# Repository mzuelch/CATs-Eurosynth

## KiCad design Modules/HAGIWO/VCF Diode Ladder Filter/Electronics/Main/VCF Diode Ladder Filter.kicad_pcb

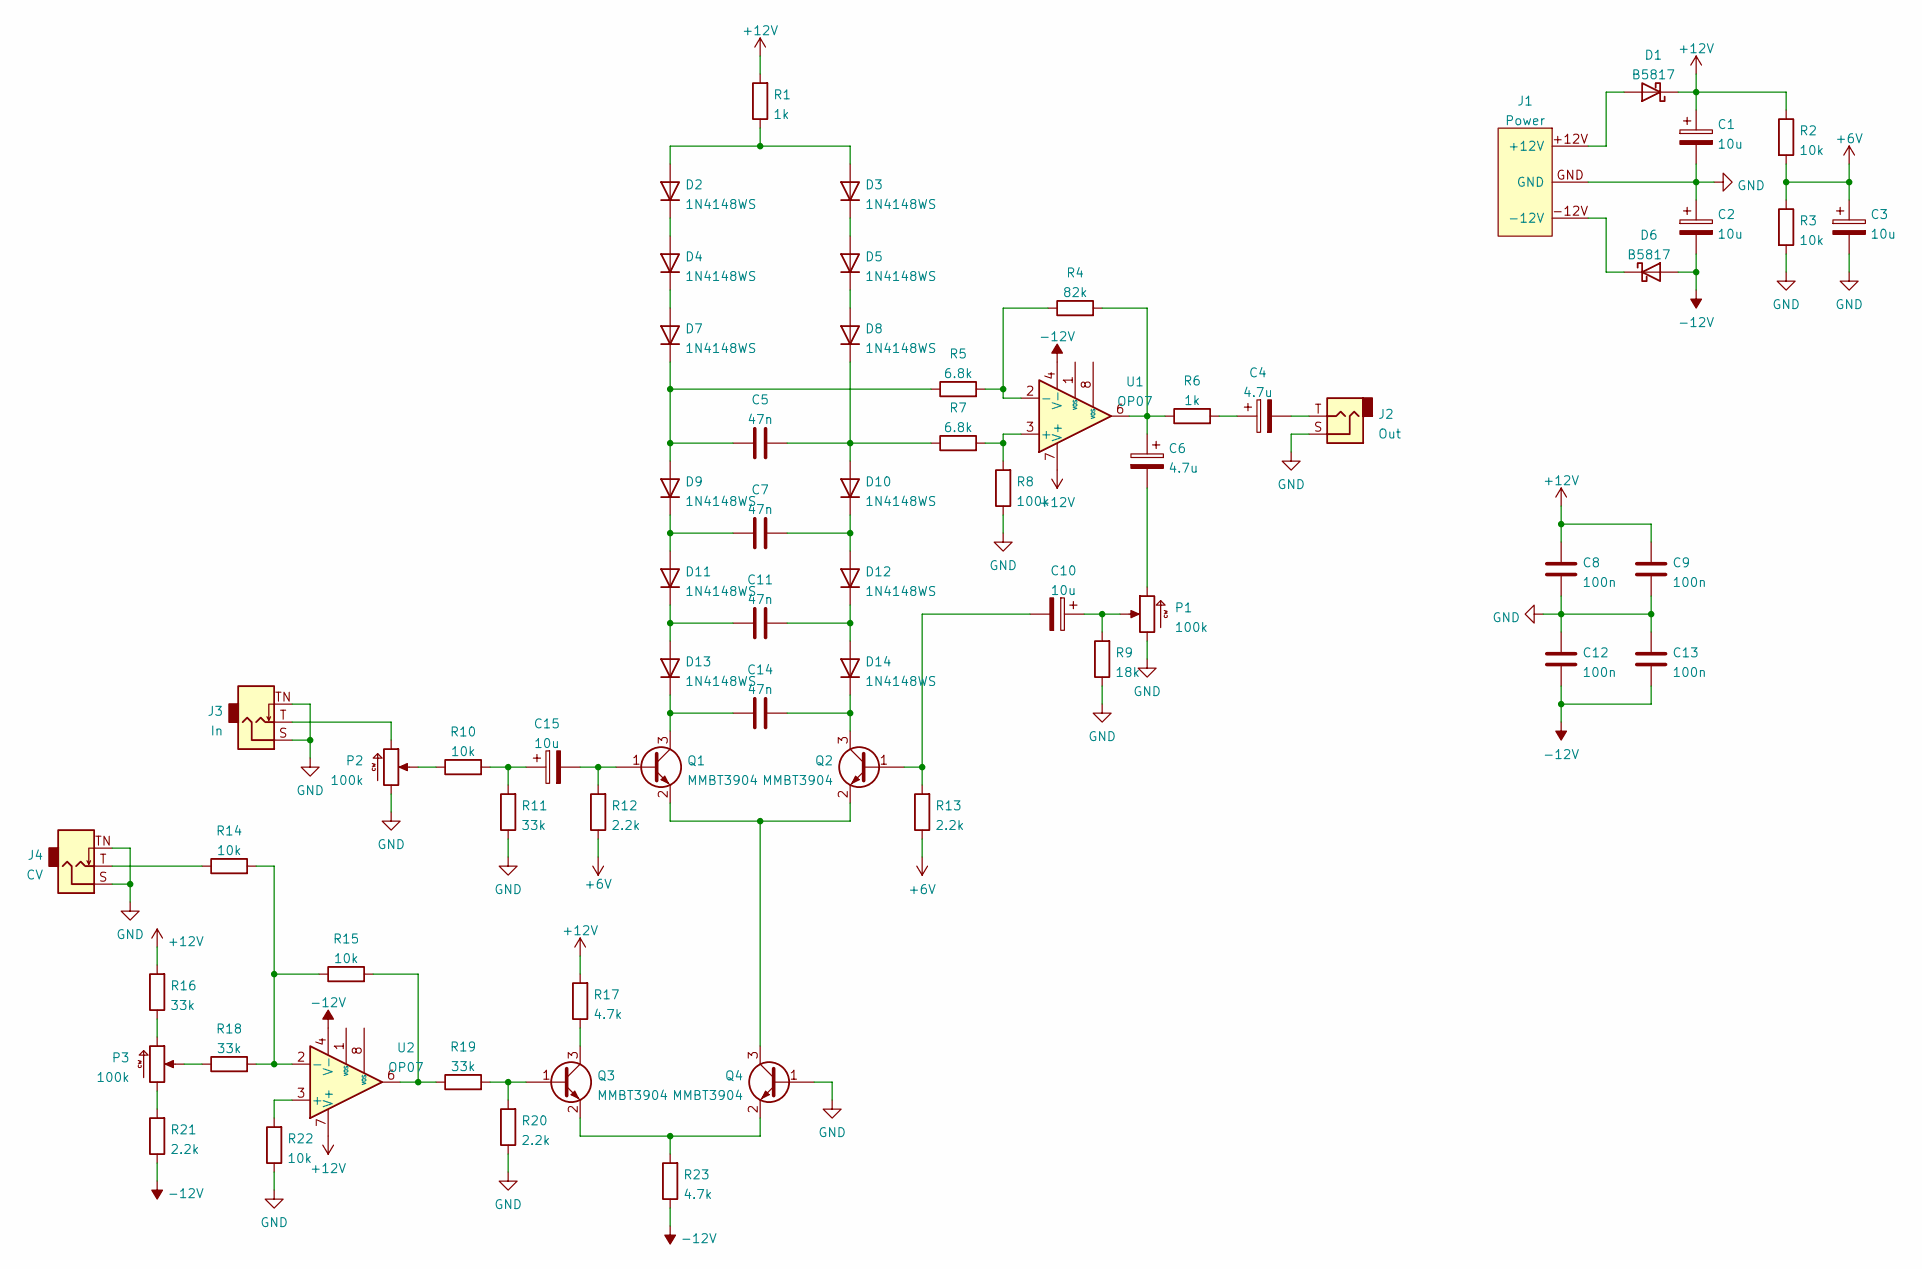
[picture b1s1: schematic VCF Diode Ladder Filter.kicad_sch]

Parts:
C1, C2, C3, C10, C15: 10u; CP_Elec_4x5.4; LCSC C72485
C4, C6: 4.7u; CP_Elec_6.3x5.4; LCSC C90266
C5, C7, C11, C14: 47n; C_1206_3216Metric; LCSC C21812
C8, C9, C12, C13: 100n; C_0402_1005Metric; LCSC C307331
D1, D6: B5817; D_SOD-323; LCSC C122854
D2, D3, D4, D5, D7, D8, D9, D10, D11, D12, D13, D14: 1N4148WS; D_SOD-323; LCSC C2128
J1: Power; Power_2x5_Vertical
J2: Out; Jack_3.5mm_QingPu_WQP-PJ301M-12
J3: In; Jack_3.5mm_QingPu_WQP-PJ301M-12
J4: CV; Jack_3.5mm_QingPu_WQP-PJ301M-12
P1, P3: 100k; Potentiometer_AlpsAlpine_RK09L1140
P2: 100k; Potentiometer_AlpsAlpine_RK09K1130
Q1, Q2, Q3, Q4: MMBT3904; SOT-23; LCSC C20526
R1, R6: 1k; R_0402_1005Metric; LCSC C25905
R2, R3, R10, R14, R15, R22: 10k; R_0402_1005Metric; LCSC C25744
R4: 82k; R_0402_1005Metric; LCSC C4142
R5, R7: 6.8k; R_0402_1005Metric; LCSC C25917
R8: 100k; R_0402_1005Metric; LCSC C25741
R9: 18k; R_0402_1005Metric; LCSC C25762
R11, R16, R18, R19: 33k; R_0402_1005Metric; LCSC C25779
R12, R13, R20, R21: 2.2k; R_0402_1005Metric; LCSC C25879
R17, R23: 4.7k; R_0402_1005Metric; LCSC C25900
U1, U2: OP07; SOIC-8_3.9x4.9mm_P1.27mm; LCSC C7433

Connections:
+6V: C3.1, R2.2, R3.1, R12.1, R13.1
+12V: C1.1, C8.1, C9.1, D1.1 (K), R1.2, R2.1, R16.2, R17.2, U1.7 (V+), U2.7 (V+)
-12V: C2.2, C12.2, C13.2, D6.2 (A), R21.1, R23.1, U1.4 (V-), U2.4 (V-)
GND: C1.2, C2.1, C3.2, C8.2, C9.2, C12.1, C13.1, J1.GND, J2.S, J3.S, J3.TN, J4.S, J4.TN, P1.CCW, P2.CCW, Q4.1 (B), R3.2, R8.1, R9.1, R11.1, R20.1, R22.1
unnamed: C4.1, R6.2
unnamed: C4.2, J2.T
unnamed: C5.1, D7.1 (K), D9.2 (A), R5.1
unnamed: C5.2, D8.1 (K), D10.2 (A), R7.1
unnamed: C6.1, R4.2, R6.1, U1.6
unnamed: C6.2, P1.CW
unnamed: C7.1, D9.1 (K), D11.2 (A)
unnamed: C7.2, D10.1 (K), D12.2 (A)
unnamed: C10.1, P1.W, R9.2
unnamed: C10.2, Q2.1 (B), R13.2
unnamed: C11.1, D11.1 (K), D13.2 (A)
unnamed: C11.2, D12.1 (K), D14.2 (A)
unnamed: C14.1, D13.1 (K), Q1.3 (C)
unnamed: C14.2, D14.1 (K), Q2.3 (C)
unnamed: C15.1, R10.2, R11.2
unnamed: C15.2, Q1.1 (B), R12.2
unnamed: D1.2 (A), J1.+12V
unnamed: D2.1 (K), D4.2 (A)
unnamed: D2.2 (A), D3.2 (A), R1.1
unnamed: D3.1 (K), D5.2 (A)
unnamed: D4.1 (K), D7.2 (A)
unnamed: D5.1 (K), D8.2 (A)
unnamed: D6.1 (K), J1.-12V
unnamed: J3.T, P2.CW
unnamed: J4.T, R14.1
unnamed: P2.W, R10.1
unnamed: P3.CCW, R21.2
unnamed: P3.CW, R16.1
unnamed: P3.W, R18.1
unnamed: Q1.2 (E), Q2.2 (E), Q4.3 (C)
unnamed: Q3.1 (B), R19.2, R20.2
unnamed: Q3.2 (E), Q4.2 (E), R23.2
unnamed: Q3.3 (C), R17.1
unnamed: R4.1, R5.2, U1.2 (-)
unnamed: R7.2, R8.2, U1.3 (+)
unnamed: R14.2, R15.1, R18.2, U2.2 (-)
unnamed: R15.2, R19.1, U2.6
unnamed: R22.2, U2.3 (+)

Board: 2 copper layers, 65 parts (59 on the bottom side), 42 nets, no tracks yet.

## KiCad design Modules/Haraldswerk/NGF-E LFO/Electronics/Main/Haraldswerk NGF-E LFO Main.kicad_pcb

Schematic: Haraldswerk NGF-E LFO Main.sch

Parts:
C1: 1µF; C_Disc_D4.7mm_W2.5mm_P5.00mm
C2, C3: 10µF; CP_Radial_D4.0mm_P1.50mm
C4, C5, C6, C7, C8, C9: 100n; C_Disc_D4.7mm_W2.5mm_P5.00mm
C10: 10µF; C_Disc_D4.7mm_W2.5mm_P5.00mm
C11: 2.2µF; C_Disc_D4.7mm_W2.5mm_P5.00mm
D1, D2: LED; LED_D3.0mm
D3, D4: B5819; D_DO-41_SOD81_P7.62mm_Horizontal
J1: SAW_UP; Jack_3.5mm_QingPu_WQP-PJ323M
J2: SAW_DOWN; Jack_3.5mm_QingPu_WQP-PJ323M
J3: TRIANGLE; Jack_3.5mm_QingPu_WQP-PJ323M
J4: SQUARE; Jack_3.5mm_QingPu_WQP-PJ323M
J5: Power; Power_2x5_Vertical
J6: Select; PinHeader_2x03_P2.54mm_Vertical
Q1: BC547; TO-92_Inline
R1: 47; R_Axial_DIN0207_L6.3mm_D2.5mm_P2.54mm_Vertical
R2, R3: 68k; R_Axial_DIN0207_L6.3mm_D2.5mm_P2.54mm_Vertical
R4, R5, R9, R10, R11: 100k; R_Axial_DIN0207_L6.3mm_D2.5mm_P2.54mm_Vertical
R6, R7: 2k; R_Axial_DIN0207_L6.3mm_D2.5mm_P2.54mm_Vertical
R8: 47k; R_Axial_DIN0207_L6.3mm_D2.5mm_P2.54mm_Vertical
R12, R15, R16, R17: 1k; R_Axial_DIN0207_L6.3mm_D2.5mm_P2.54mm_Vertical
R13, R14: 10k; R_Axial_DIN0207_L6.3mm_D2.5mm_P2.54mm_Vertical
R18: 2k7; R_Axial_DIN0207_L6.3mm_D2.5mm_P2.54mm_Vertical
RV1: A100k; Potentiometer_AlpsAlpine_RK0971110
T1: 1k; Potentiometer_Runtron_RM-065_Vertical
U1, U2, U3: TL072; DIP-8_W7.62mm_LongPads

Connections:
+12V: C2.1, C4.1, C6.1, C8.1, D3.1 (K), U1.8 (V+), U2.8 (V+), U3.8 (V+)
+12VA: D3.2 (A), J5.+12V
-12V: C3.2, C5.2, C7.2, C9.2, D4.2 (A), U1.4 (V-), U2.4 (V-), U3.4 (V-)
-12VA: D4.1 (K), J5.-12V
GND: C2.2, C3.1, C4.2, C5.1, C6.2, C7.1, C8.2, C9.1, J1.S, J2.S, J3.S, J4.S, J5.GND, Q1.3 (E), R1.1, R3.1, R7.1, U1.6 (-), U2.5 (+), U3.5 (+)
unnamed: C1.2, J6.6
unnamed: C10.2, J6.2
unnamed: C11.2, J6.4
unnamed: D1.1 (K), D2.2 (A), U3.7
unnamed: D1.2 (A), D2.1 (K), R18.2, U3.6 (-)
unnamed: J1.T, R12.1
unnamed: J2.T, R15.1
unnamed: J3.T, R16.1
unnamed: J4.T, R17.1
unnamed: J6.1, J6.3, J6.5, R2.1, U1.2 (-)
unnamed: Q1.1 (C), R10.1, U2.3 (+)
unnamed: Q1.2 (B), R8.1
unnamed: R3.2, U1.3 (+)
unnamed: R4.1, R5.2, U1.5 (+)
unnamed: R6.1, T1.3
unnamed: R6.2, U1.7
unnamed: R7.2, T1.1
unnamed: R11.1, R12.2, R13.2, U2.1
unnamed: R9.1, R11.2, U2.2 (-)
unnamed: R13.1, R14.2, U2.6 (-)
unnamed: R14.1, R15.2, U2.7
unnamed: R17.2, U3.1, U3.2 (-)
SQR: R5.1, R8.2, T1.2, U3.3 (+)
TRI: C1.1, C10.1, C11.1, R4.2, R9.2, R10.2, R16.2, R18.1, U1.1

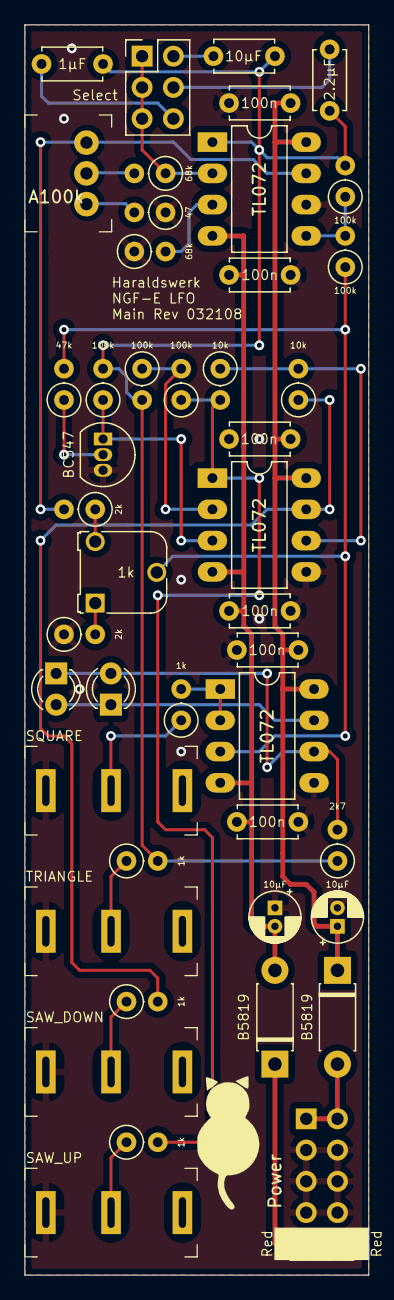
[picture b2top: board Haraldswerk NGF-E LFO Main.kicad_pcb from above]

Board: 2 copper layers, 27.9 x 101.6 mm, 45 parts (0 on the bottom side), 29 nets.

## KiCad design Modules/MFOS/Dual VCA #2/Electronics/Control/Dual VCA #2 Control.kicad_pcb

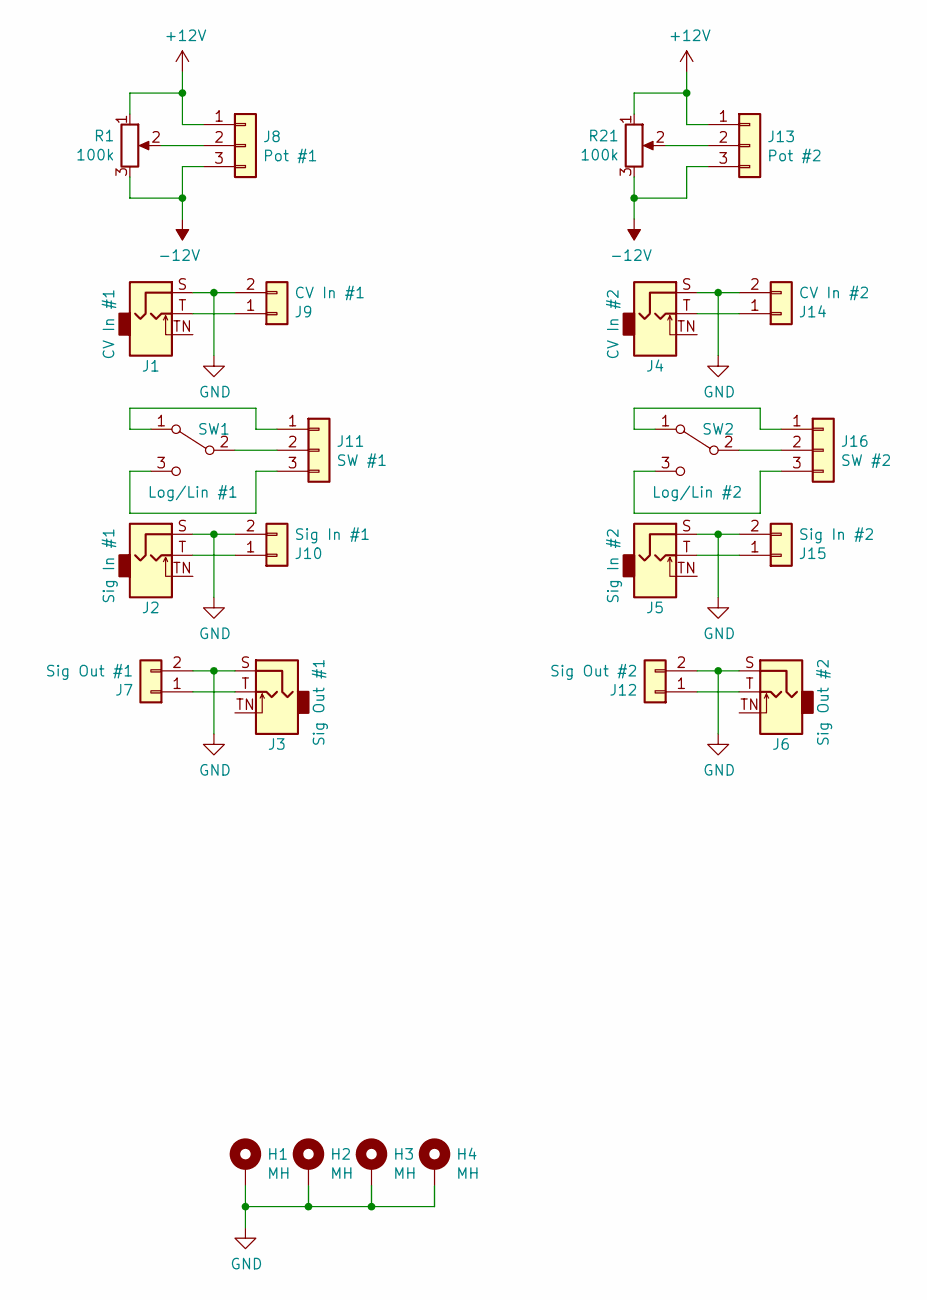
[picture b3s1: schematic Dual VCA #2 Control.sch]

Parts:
H1, H2, H3, H4: MH; MountingHole_2.7mm_M2.5_DIN965_Pad
J1: CV In #1; PJ-301-M-12
J2: Sig In #1; PJ-301-M-12
J3: Sig Out #1; PJ-301-M-12
J4: CV In #2; PJ-301-M-12
J5: Sig In #2; PJ-301-M-12
J6: Sig Out #2; PJ-301-M-12
J7: Sig Out #1; PinSocket_1x02_P2.54mm_Vertical
J8: Pot #1; PinSocket_1x03_P2.54mm_Vertical
J9: CV In #1; PinSocket_1x02_P2.54mm_Vertical
J10: Sig In #1; PinSocket_1x02_P2.54mm_Vertical
J11: SW #1; PinSocket_1x03_P2.54mm_Vertical
J12: Sig Out #2; PinSocket_1x02_P2.54mm_Vertical
J13: Pot #2; PinSocket_1x03_P2.54mm_Vertical
J14: CV In #2; PinSocket_1x02_P2.54mm_Vertical
J15: Sig In #2; PinSocket_1x02_P2.54mm_Vertical
J16: SW #2; PinSocket_1x03_P2.54mm_Vertical
R1, R21: 100k; Potentiometer_Alps_RK09L_Single_Vertical
SW1: Log/Lin #1; SMTS-1xx-Solder
SW2: Log/Lin #2; SMTS-1xx-Solder

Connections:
+12V: J8.1, J13.1, R1.1, R21.1
-12V: J8.3, J13.3, R1.3, R21.3
GND: H1.1, H2.1, H3.1, H4.1, J1.S, J2.S, J3.S, J4.S, J5.S, J6.S, J7.2, J9.2, J10.2, J12.2, J14.2, J15.2
unnamed: J1.T, J9.1
unnamed: J3.T, J7.1
unnamed: J8.2, R1.2
unnamed: J2.T, J10.1
unnamed: J11.1, SW1.1 (A)
unnamed: J11.2, SW1.2 (B)
unnamed: J11.3, SW1.3 (C)
unnamed: J6.T, J12.1
unnamed: J13.2, R21.2
unnamed: J4.T, J14.1
unnamed: J5.T, J15.1
unnamed: J16.1, SW2.1 (A)
unnamed: J16.2, SW2.2 (B)
unnamed: J16.3, SW2.3 (C)

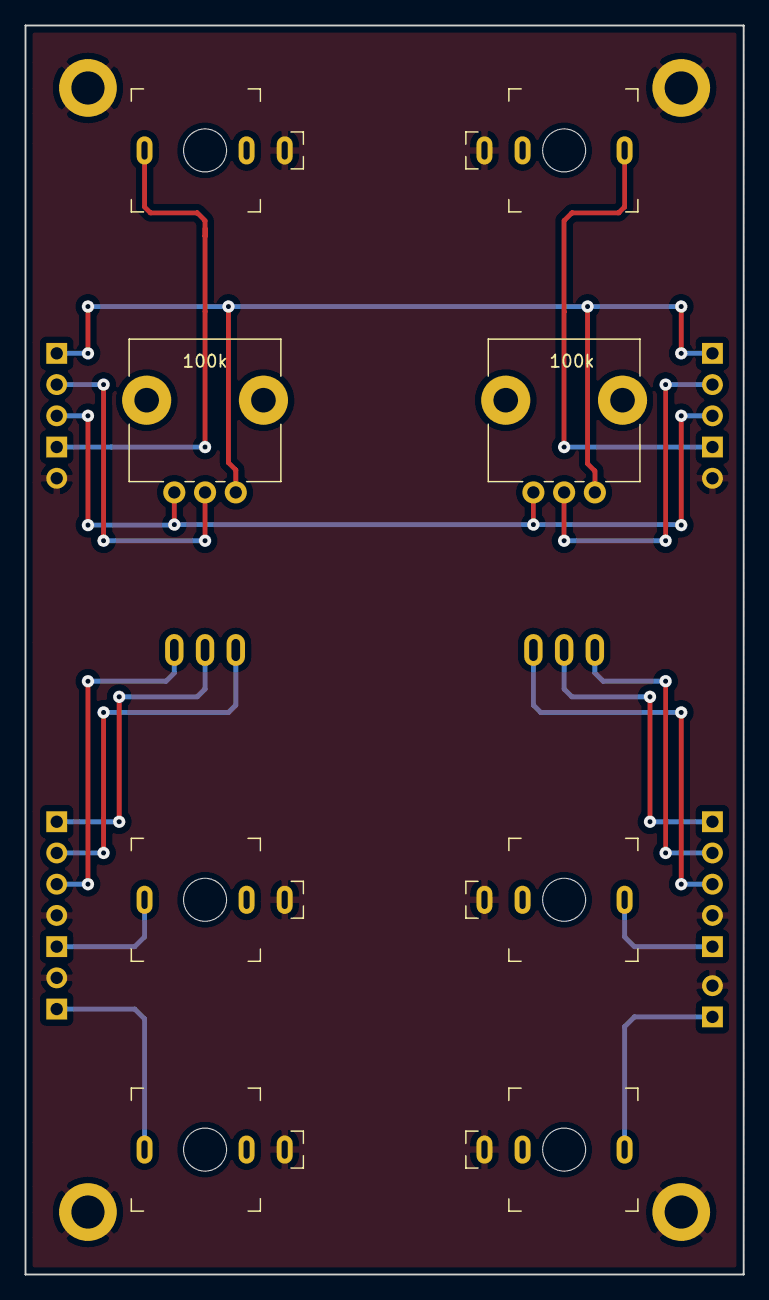
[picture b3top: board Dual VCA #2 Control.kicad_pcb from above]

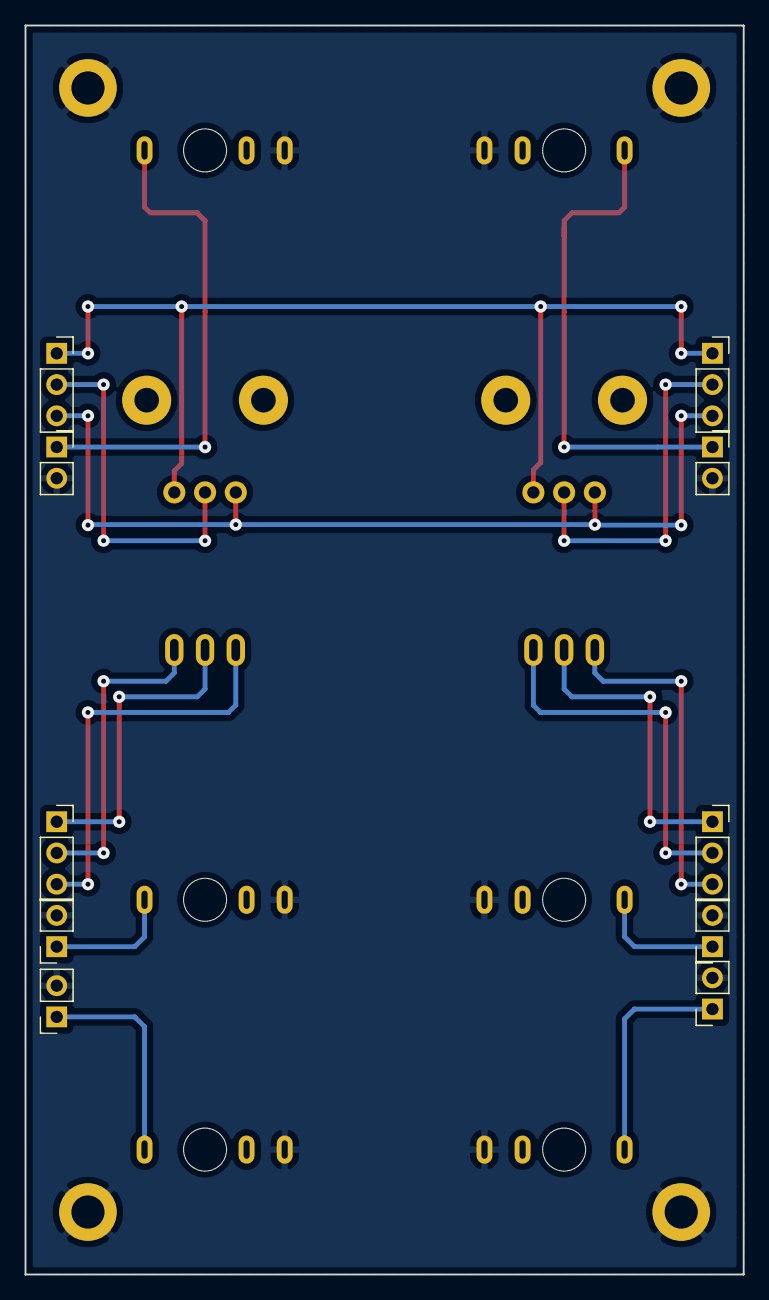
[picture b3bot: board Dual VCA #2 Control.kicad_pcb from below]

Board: 2 copper layers, 58.4 x 101.6 mm, 24 parts (10 on the bottom side), 17 nets.

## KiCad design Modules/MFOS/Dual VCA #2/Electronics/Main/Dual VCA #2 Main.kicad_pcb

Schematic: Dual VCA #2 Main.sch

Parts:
C1, C2: 10µF/63V; CP_Radial_D5.0mm_P2.50mm
C3, C4, C5, C6: 100n; C_Disc_D3.0mm_W2.0mm_P2.50mm
D1, D2: 1N5817; D_DO-41_SOD81_P10.16mm_Horizontal
H1, H2, H3, H4: MH; MountingHole_2.7mm_M2.5_DIN965_Pad
IC1: TL084; DIP-14_W7.62mm_Socket_LongPads
IC2: LM13700; DIP-16_W7.62mm_Socket_LongPads
J1: Pot #1; PinHeader_1x03_P2.54mm_Vertical
J2: CV In #1; PinHeader_1x02_P2.54mm_Vertical
J3: Sig In #1; PinHeader_1x02_P2.54mm_Vertical
J4: SW #1; PinHeader_1x03_P2.54mm_Vertical
J5: Sig Out #1; PinHeader_1x02_P2.54mm_Vertical
J6: Pot #2; PinHeader_1x03_P2.54mm_Vertical
J7: Power; Power_2x5_Vertical
J8: CV In #2; PinHeader_1x02_P2.54mm_Vertical
J9: Sig In #2; PinHeader_1x02_P2.54mm_Vertical
J10: SW #2; PinHeader_1x03_P2.54mm_Vertical
J11: Sig Out #2; PinHeader_1x02_P2.54mm_Vertical
Q1, Q3: 2N3904; TO-92_Inline
Q2, Q4: 2N3906; TO-92_Inline
R2, R6, R7, R10, R17, R22, R26, R27, R30, R37: 100k; R_Axial_DIN0207_L6.3mm_D2.5mm_P7.62mm_Horizontal
R3: 2k; R_Axial_DIN0207_L6.3mm_D2.5mm_P5.08mm_Vertical
R4, R24: 2k; R_Axial_DIN0207_L6.3mm_D2.5mm_P12.70mm_Horizontal
R5, R25: 100k; R_Axial_DIN0207_L6.3mm_D2.5mm_P5.08mm_Vertical
R8: 2k; R_Axial_DIN0207_L6.3mm_D2.5mm_P7.62mm_Horizontal
R9, R29: 120k; R_Axial_DIN0207_L6.3mm_D2.5mm_P7.62mm_Horizontal
R11, R31: 470R; R_Axial_DIN0207_L6.3mm_D2.5mm_P7.62mm_Horizontal
R12, R13, R32, R33: 20k; R_Axial_DIN0207_L6.3mm_D2.5mm_P7.62mm_Horizontal
R14, R34: 30k; R_Axial_DIN0207_L6.3mm_D2.5mm_P7.62mm_Horizontal
R15, R35: 470k; R_Axial_DIN0207_L6.3mm_D2.5mm_P7.62mm_Horizontal
R16, R36: 47k; R_Axial_DIN0207_L6.3mm_D2.5mm_P7.62mm_Horizontal
R18, R38: 220R; R_Axial_DIN0207_L6.3mm_D2.5mm_P7.62mm_Horizontal
R19, R39: 4k7; R_Axial_DIN0207_L6.3mm_D2.5mm_P7.62mm_Horizontal
R20, R40: 1k; R_Axial_DIN0207_L6.3mm_D2.5mm_P7.62mm_Horizontal
R23, R28: 2k; R_Axial_DIN0207_L6.3mm_D2.5mm_P2.54mm_Vertical

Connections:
+12V: C1.1, C3.1, C4.1, D1.1, IC1.4 (V+), IC2.11 (V+), J1.1, J6.1, Q1.3 (C), Q3.3 (C), R7.2, R10.2, R15.2, R27.2, R30.2, R35.2
+12VA: D1.2, J7.+12V
-12V: C2.2, C5.2, C6.2, D2.2, IC1.11 (V-), IC2.6 (V-), J1.3, J6.3, R9.1, R13.1, R19.1, R29.1, R33.1, R39.1
-12VA: D2.1, J7.-12V
GND: C1.2, C2.1, C3.2, C4.2, C5.1, C6.1, H1.1, H2.1, H3.1, H4.1, IC2.4 (-), IC2.13 (-), J2.2, J3.2, J5.2, J7.GND, J8.2, J9.2, J11.2, Q2.1 (E), Q4.1 (E), R8.1, R11.1, R16.2, R18.1, R28.1, R31.1, R36.2, R38.1
unnamed: IC1.1, R25.1, R34.2
unnamed: IC1.2 (-), R24.1, R25.2
unnamed: IC1.3 (+), R30.1, R31.2
unnamed: IC1.5 (+), R27.1, R28.2
unnamed: IC1.6 (-), R22.1, R23.2, R26.1
unnamed: IC1.7, Q3.2 (B), R23.1, R24.2
unnamed: IC1.8, Q1.2 (B), R3.1, R4.2
unnamed: IC1.9 (-), R2.1, R3.2, R6.1
unnamed: IC1.10 (+), R7.1, R8.2
unnamed: IC1.12 (+), R10.1, R11.2
unnamed: IC1.13 (-), R4.1, R5.2
unnamed: IC1.14, R5.1, R14.2
unnamed: IC2.1, J4.1
unnamed: IC2.3 (+), R17.1, R18.2
unnamed: IC2.5, IC2.7, R15.1, R16.1
unnamed: IC2.8, R19.2, R20.2
unnamed: IC2.9, R39.2, R40.2
unnamed: IC2.10, IC2.12, R35.1, R36.1
unnamed: IC2.14 (+), R37.1, R38.2
unnamed: IC2.16, J10.1
unnamed: J1.2, R2.2
unnamed: J2.1, R6.2
unnamed: J3.1, R17.2
unnamed: J4.2, R12.1
unnamed: J4.3, R13.2, R14.1
unnamed: J5.1, R20.1
unnamed: J6.2, R22.2
unnamed: J8.1, R26.2
unnamed: J9.1, R37.2
unnamed: J10.2, R32.1
unnamed: J10.3, R33.2, R34.1
unnamed: J11.1, R40.1
unnamed: Q1.1 (E), Q2.2 (B), R9.2
unnamed: Q2.3 (C), R12.2
unnamed: Q3.1 (E), Q4.2 (B), R29.2
unnamed: Q4.3 (C), R32.2

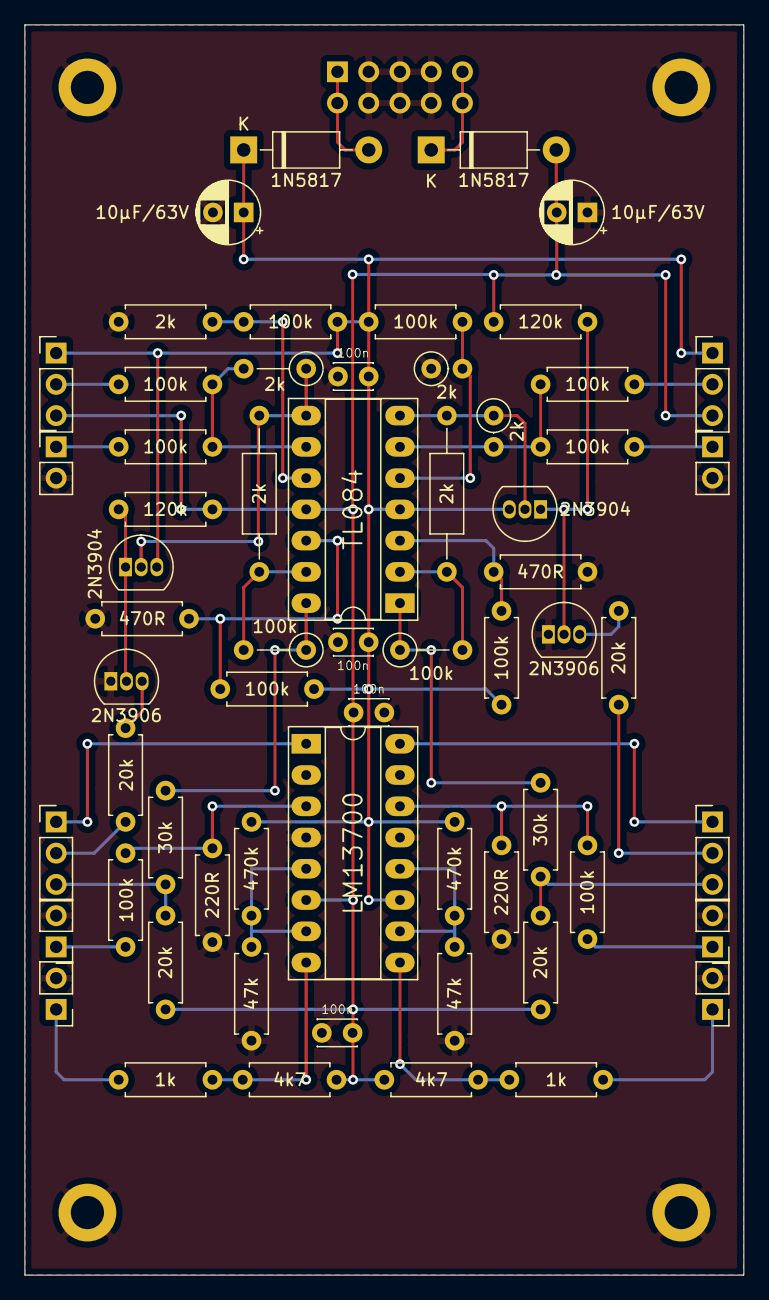
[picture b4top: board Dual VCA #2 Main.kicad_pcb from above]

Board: 2 copper layers, 58.4 x 101.6 mm, 67 parts (1 on the bottom side), 41 nets.

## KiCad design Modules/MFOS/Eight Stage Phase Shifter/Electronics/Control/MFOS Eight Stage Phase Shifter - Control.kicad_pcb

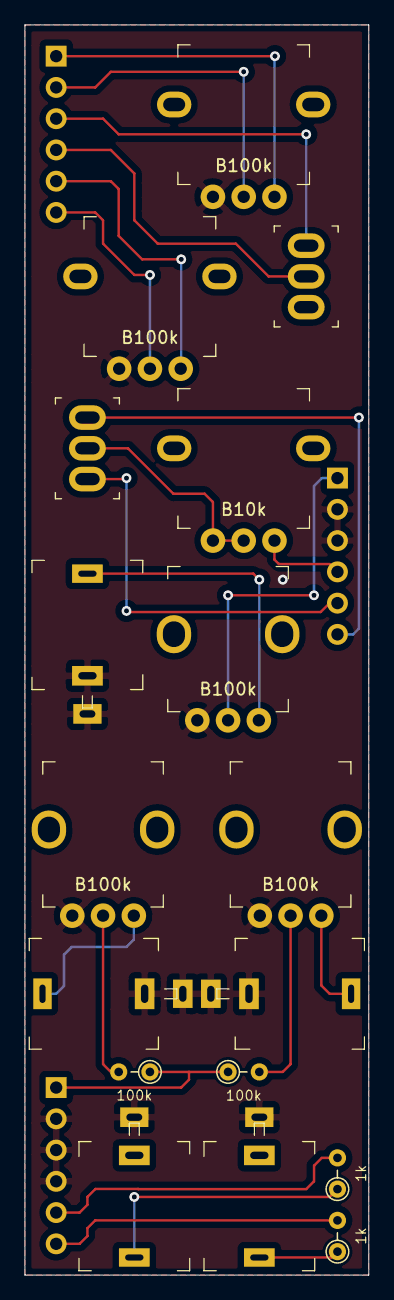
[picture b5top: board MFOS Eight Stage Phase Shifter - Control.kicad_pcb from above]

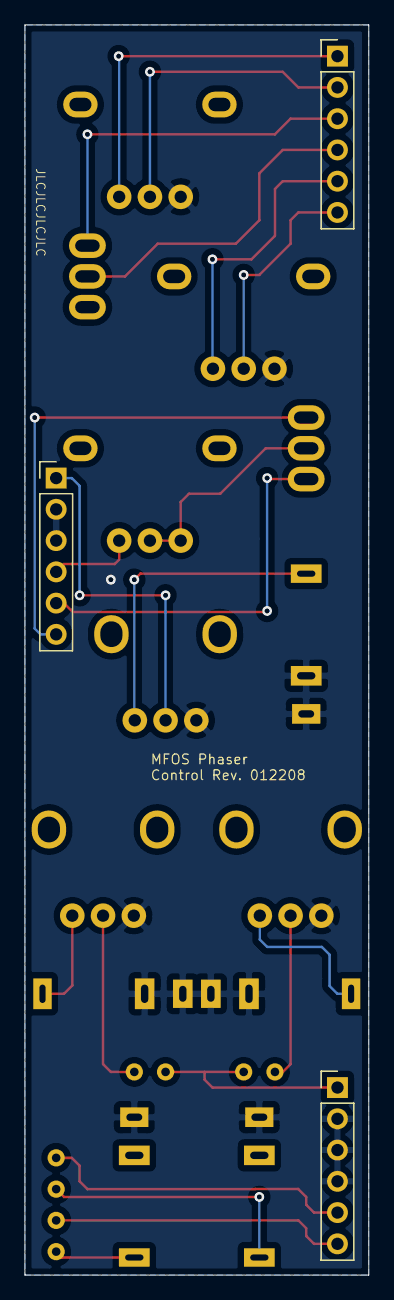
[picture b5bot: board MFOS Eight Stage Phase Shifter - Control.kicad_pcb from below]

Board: 2 copper layers, 27.9 x 101.6 mm, 20 parts (3 on the bottom side), 22 nets.

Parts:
J1: LFO; PinHeader_1x06_P2.54mm_Vertical
J2: CV_OUT; PinHeader_1x06_P2.54mm_Vertical
J3: In; PinHeader_1x06_P2.54mm_Vertical
J4: CV1; Jack_3.5mm_QingPu_WQP-PJ301M-12
J5: CV2; Jack_3.5mm_QingPu_WQP-PJ301M-12
J6: In; Jack_3.5mm_QingPu_WQP-PJ301M-12
J7: Out1; Jack_3.5mm_QingPu_WQP-PJ301M-12
J8: Out2; Jack_3.5mm_QingPu_WQP-PJ301M-12
P1, P2, P3: B100k; Potentiometer_AlpsAlpine_RK09K1130
P4, P6: B100k; Potentiometer_AlpsAlpine_RK09L1140
P5: B10k; Potentiometer_AlpsAlpine_RK09L1140
R1, R2: 1k; R_Axial_DIN0204_L3.6mm_D1.6mm_P2.54mm_Vertical
R3, R4: 100k; R_Axial_DIN0204_L3.6mm_D1.6mm_P2.54mm_Vertical
SW1: Stages; Switches_SMTS-10x
SW2: Mode; Switches_SMTS-10x

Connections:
CV: J2.1, R3.1, R4.1
Depth_CW: J1.5, P6.CW
Depth_W: J1.6, P6.W
FB: J3.4, P5.CW
GND: J2.2, J2.3, J2.4, J3.2, J3.3, J4.S, J4.TN, J5.S, J5.TN, J6.S, J6.TN, J7.S, J8.S, P1.CCW, P2.CCW, P3.CCW, P4.CCW, P6.CCW
In: J3.1, P3.W
Mode_In: J1.3, SW2.1
Mode_Out: J1.4, SW2.2
unnamed: J4.T, P1.CW
unnamed: J5.T, P2.CW
unnamed: J6.T, P3.CW
unnamed: J7.T, R1.1
unnamed: J8.T, R2.1
unnamed: P1.W, R3.2
unnamed: P2.W, R4.2
unnamed: P5.CCW, P5.W, SW1.2
OUT4: J3.5, SW1.1
OUT8: J3.6, SW1.3
Out1: J2.5, R1.2
Out2: J2.6, R2.2
Rate_CW: J1.1, P4.CW
Rate_W: J1.2, P4.W
